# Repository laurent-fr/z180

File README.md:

# Micro Z180 homebrew computer

*This is my attempt to create a 80's style computer based on the Zilog Z180 CPU.*

The goal is to build from scratch a complete computer, with  keyboard, video display, and mass storage. The software will be Microsoft BASIC and CP/M. Think of it as a crossover between an Amstrad CPC and an IBM PC 5150 !

The computer is designed around STEBUS, which is an old but well designed 8-bits industry-standard bus (https://en.wikipedia.org/wiki/STEbus). 

For now there are 5 cards :

 * PSU : the power supply, which takes 12v as input and generates +5v and -12v 
 * BUS : the STEBUS base board, with 5 slots and active termination
 * CPU : The main CPU board, with 2 RS-232 connectors
 * VDU : Video display unit, VGA text-only 80x25 with 16 colors, and 8 fonts selectable via jumpers on the board
 * MIO : Multi I/O, including PS/2 keyboard, Real time clock, Sound , Compact flash and Parallel port
 
 There are 3 main folders in this reposirory :
 
 * enclosure : all the files needed to build the case, which is laser-cut 3mm transparent acrylic (all parts are smaller than 200x300 mm), with a 3D printed part to mechanicaly guide the boards.
 * hardware : the description of all boards (very incomplete for now !)
 * software : Tests, BIOS, BASIC, and CP/M (coming soon !)
 
 ## Licenses
 
All the software is GPL v2, and all the hardware is CC-BY-NC-SA
 
 ## Status of the computer
 
 **This is a work-in-progress !**
 
 For now the computer is running BASIC with the PS/2 keyboard and integrated video display. There are still some rough edges but we are almost here.
 
 Some files are not yet on the repository because the computer was designed with paper and pencil !

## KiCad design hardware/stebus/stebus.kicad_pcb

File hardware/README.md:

# Hardware

## Software needed

A few softwares are needed for reading/using the files in this folder :

* Kicad for reading the schematics and board layouts  https://kicad-pcb.org/ 
* Quartus 2 web edition for programming the Altera CPLDs https://fpgasoftware.intel.com/13.1/?edition=web
* WinCUPL for programming the GAL of the VDU board https://www.microchip.com/design-centers/fpgas-and-plds/splds-cplds/pld-design-resources

Optional :

* LTSPice, if you want to look at the few simulation files https://www.analog.com/en/design-center/design-tools-and-calculators/ltspice-simulator.html

## Hardware needed for running the computer

* An EPROM programmer. I use a Minipro TL866.
* A JTAG programmer for the CPLDs. I use the super cheap USB Blaster.

## Hardware for debugging the computer

It is not strictly needed to build the computer from the blueprints, but if something goes wrong the following could help :

* An EPROM simulator. The fastest way to test a new firmware ! Mine is a MemSIM2 from http://www.momik.pl/ and it works very well.
* A logic analyzer. Pick your favourite. Mine is a DSLogic.
* A good old oscilloscope is useful, too !

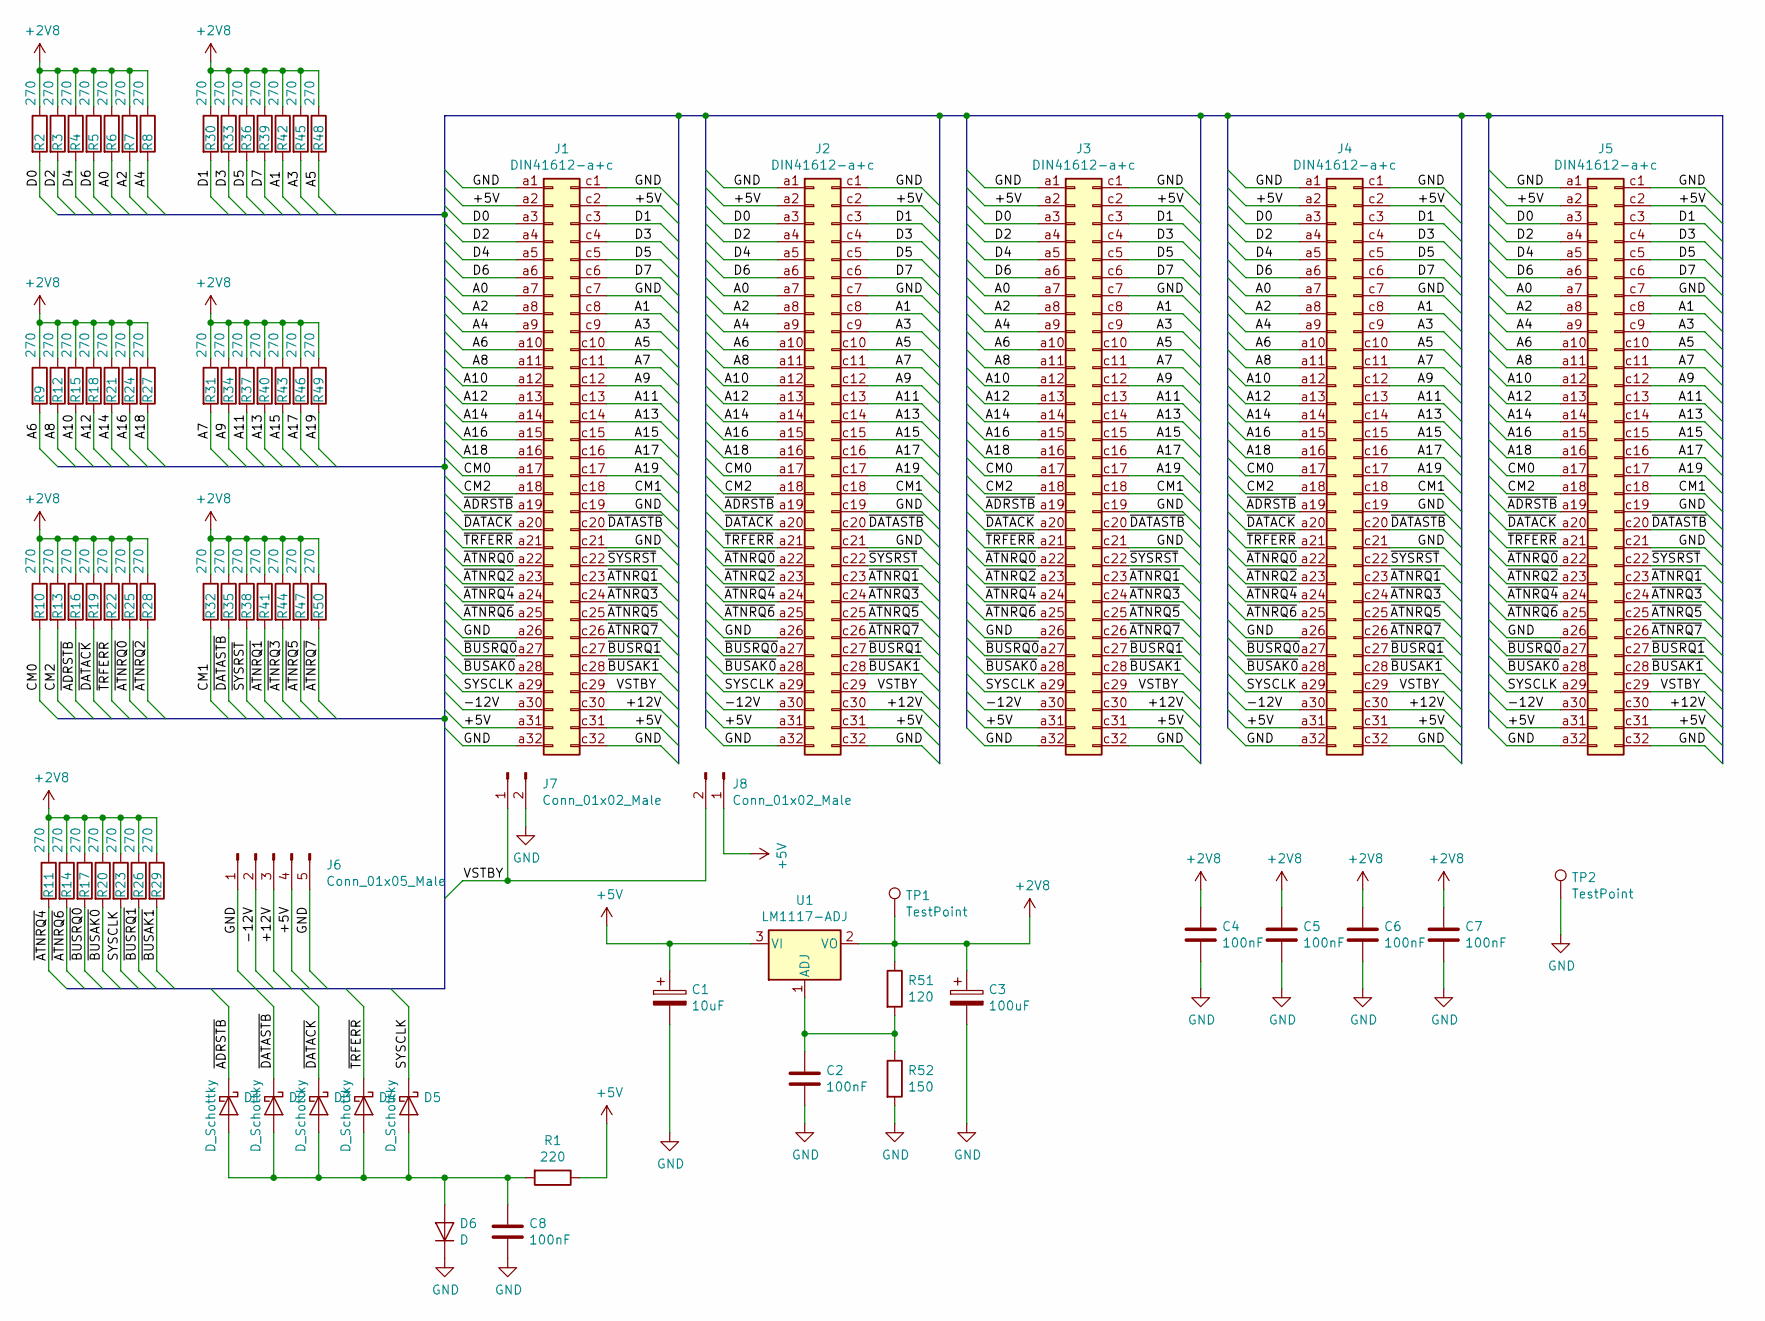
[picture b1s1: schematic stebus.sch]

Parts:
C1: 10uF; C_1210_HandSoldering
C2, C4, C5, C6, C7, C8: 100nF; C_1206_HandSoldering
C3: 100uF; C_1812_HandSoldering
D1, D2, D3, D4, D5: D_Schottky; D_SMA
D6: D; D_MiniMELF_Handsoldering
J1, J2, J3, J4, J5: DIN41612-a+c; Socket_DIN41612-CaseC1-AC-Female-64Pin-2rows
J6: Conn_01x05_Male; Molex_MiniFit-JR-5556-10A_1x05x4.20mm_Straight
J7: Conn_01x02_Male; Molex_KK-6410-02_02x2.54mm_Straight
J8: Conn_01x02_Male; Pin_Header_Straight_1x02_Pitch2.54mm
R1: 220; R_1206_HandSoldering
R2, R3, R4, R5, R6, R7, R8, R9, R10, R11, R12, R13, R14, R15, R16, R17, R18, R19, R20, R21, R22, R23, R24, R25, R26, R27, R28, R29, R30, R31, R32, R33, R34, R35, R36, R37, R38, R39, R40, R41, R42, R43, R44, R45, R46, R47, R48, R49, R50: 270; R_1206_HandSoldering
R51: 120; C_1206_HandSoldering
R52: 150; C_1206_HandSoldering
TP1, TP2: TestPoint; Pin_Header_Straight_1x01_Pitch2.54mm
U1: LM1117-ADJ; SOT-223-3_TabPin2

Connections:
+2V8: C3.1, C4.1, C5.1, C6.1, C7.1, R2.1, R3.1, R4.1, R5.1, R6.1, R7.1, R8.1, R9.1, R10.1, R11.1, R12.1, R13.1, R14.1, R15.1, R16.1, R17.1, R18.1, R19.1, R20.1, R21.1, R22.1, R23.1, R24.1, R25.1, R26.1, R27.1, R28.1, R29.1, R30.1, R31.1, R32.1, R33.1, R34.1, R35.1, R36.1, R37.1, R38.1, R39.1, R40.1, R41.1, R42.1, R43.1, R44.1, R45.1, R46.1, R47.1, R48.1, R49.1, R50.1, R51.1, TP1.1, U1.2 (VO)
+5V: C1.1, J1.a2, J1.a31, J1.c2, J1.c31, J2.a2, J2.a31, J2.c2, J2.c31, J3.a2, J3.a31, J3.c2, J3.c31, J4.a2, J4.a31, J4.c2, J4.c31, J5.a2, J5.a31, J5.c2, J5.c31, J6.4, J8.1, R1.1, U1.3 (VI)
/+12V: J1.c30, J2.c30, J3.c30, J4.c30, J5.c30, J6.3
/-12V: J1.a30, J2.a30, J3.a30, J4.a30, J5.a30, J6.2
/A0: J1.a7, J2.a7, J3.a7, J4.a7, J5.a7, R6.2
/A1: J1.c8, J2.c8, J3.c8, J4.c8, J5.c8, R42.2
/A2: J1.a8, J2.a8, J3.a8, J4.a8, J5.a8, R7.2
/A3: J1.c9, J2.c9, J3.c9, J4.c9, J5.c9, R45.2
/A4: J1.a9, J2.a9, J3.a9, J4.a9, J5.a9, R8.2
/A5: J1.c10, J2.c10, J3.c10, J4.c10, J5.c10, R48.2
/A6: J1.a10, J2.a10, J3.a10, J4.a10, J5.a10, R9.2
/A7: J1.c11, J2.c11, J3.c11, J4.c11, J5.c11, R31.2
/A8: J1.a11, J2.a11, J3.a11, J4.a11, J5.a11, R12.2
/A9: J1.c12, J2.c12, J3.c12, J4.c12, J5.c12, R34.2
/A10: J1.a12, J2.a12, J3.a12, J4.a12, J5.a12, R15.2
/A11: J1.c13, J2.c13, J3.c13, J4.c13, J5.c13, R37.2
/A12: J1.a13, J2.a13, J3.a13, J4.a13, J5.a13, R18.2
/A13: J1.c14, J2.c14, J3.c14, J4.c14, J5.c14, R40.2
/A14: J1.a14, J2.a14, J3.a14, J4.a14, J5.a14, R21.2
/A15: J1.c15, J2.c15, J3.c15, J4.c15, J5.c15, R43.2
/A16: J1.a15, J2.a15, J3.a15, J4.a15, J5.a15, R24.2
/A17: J1.c16, J2.c16, J3.c16, J4.c16, J5.c16, R46.2
/A18: J1.a16, J2.a16, J3.a16, J4.a16, J5.a16, R27.2
/A19: J1.c17, J2.c17, J3.c17, J4.c17, J5.c17, R49.2
/CM0: J1.a17, J2.a17, J3.a17, J4.a17, J5.a17, R10.2
/CM1: J1.c18, J2.c18, J3.c18, J4.c18, J5.c18, R32.2
/CM2: J1.a18, J2.a18, J3.a18, J4.a18, J5.a18, R13.2
/D0: J1.a3, J2.a3, J3.a3, J4.a3, J5.a3, R2.2
/D1: J1.c3, J2.c3, J3.c3, J4.c3, J5.c3, R30.2
/D2: J1.a4, J2.a4, J3.a4, J4.a4, J5.a4, R3.2
/D3: J1.c4, J2.c4, J3.c4, J4.c4, J5.c4, R33.2
/D4: J1.a5, J2.a5, J3.a5, J4.a5, J5.a5, R4.2
/D5: J1.c5, J2.c5, J3.c5, J4.c5, J5.c5, R36.2
/D6: J1.a6, J2.a6, J3.a6, J4.a6, J5.a6, R5.2
/D7: J1.c6, J2.c6, J3.c6, J4.c6, J5.c6, R39.2
/SYSCLK: D5.1 (K), J1.a29, J2.a29, J3.a29, J4.a29, J5.a29, R23.2
/VSTBY: J1.c29, J2.c29, J3.c29, J4.c29, J5.c29, J7.1, J8.2
/~: J1.a25, J2.a25, J3.a25, J4.a25, J5.a25, R14.2
/~ADRSTB~: D1.1 (K), J1.a19, J2.a19, J3.a19, J4.a19, J5.a19, R16.2
/~ATNRQ0~: J1.a22, J2.a22, J3.a22, J4.a22, J5.a22, R25.2
/~ATNRQ1~: J1.c23, J2.c23, J3.c23, J4.c23, J5.c23, R41.2
/~ATNRQ2~: J1.a23, J2.a23, J3.a23, J4.a23, J5.a23, R28.2
/~ATNRQ3~: J1.c24, J2.c24, J3.c24, J4.c24, J5.c24, R44.2
/~ATNRQ4~: J1.a24, J2.a24, J3.a24, J4.a24, J5.a24, R11.2
/~ATNRQ5~: J1.c25, J2.c25, J3.c25, J4.c25, J5.c25, R47.2
/~ATNRQ7~: J1.c26, J2.c26, J3.c26, J4.c26, J5.c26, R50.2
/~BUSAK0~: J1.a28, J2.a28, J3.a28, J4.a28, J5.a28, R20.2
/~BUSAK1~: J1.c28, J2.c28, J3.c28, J4.c28, J5.c28, R29.2
/~BUSRQ0~: J1.a27, J2.a27, J3.a27, J4.a27, J5.a27, R17.2
/~BUSRQ1~: J1.c27, J2.c27, J3.c27, J4.c27, J5.c27, R26.2
/~DATACK~: D3.1 (K), J1.a20, J2.a20, J3.a20, J4.a20, J5.a20, R19.2
/~DATASTB~: D2.1 (K), J1.c20, J2.c20, J3.c20, J4.c20, J5.c20, R35.2
/~SYSRST~: J1.c22, J2.c22, J3.c22, J4.c22, J5.c22, R38.2
/~TRFERR~: D4.1 (K), J1.a21, J2.a21, J3.a21, J4.a21, J5.a21, R22.2
GND: C1.2, C2.2, C3.2, C4.2, C5.2, C6.2, C7.2, C8.2, D6.1 (K), J1.a1, J1.a26, J1.a32, J1.c1, J1.c7, J1.c19, J1.c21, J1.c32, J2.a1, J2.a26, J2.a32, J2.c1, J2.c7, J2.c19, J2.c21, J2.c32, J3.a1, J3.a26, J3.a32, J3.c1, J3.c7, J3.c19, J3.c21, J3.c32, J4.a1, J4.a26, J4.a32, J4.c1, J4.c7, J4.c19, J4.c21, J4.c32, J5.a1, J5.a26, J5.a32, J5.c1, J5.c7, J5.c19, J5.c21, J5.c32, J6.1, J6.5, J7.2, R52.2, TP2.1
unnamed: C2.1, R51.2, R52.1, U1.1 (ADJ)
unnamed: C8.1, D1.2 (A), D2.2 (A), D3.2 (A), D4.2 (A), D5.2 (A), D6.2 (A), R1.2

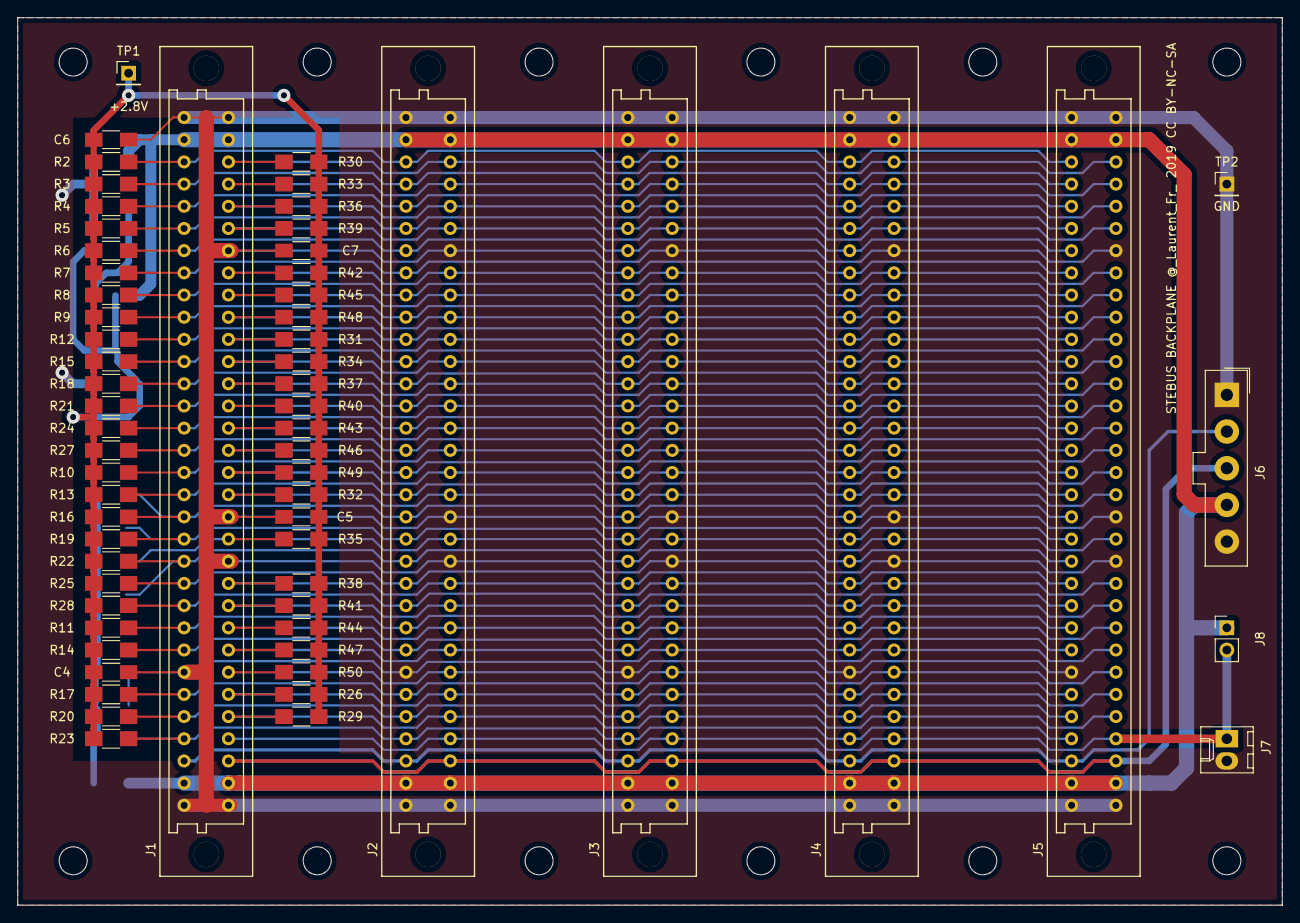
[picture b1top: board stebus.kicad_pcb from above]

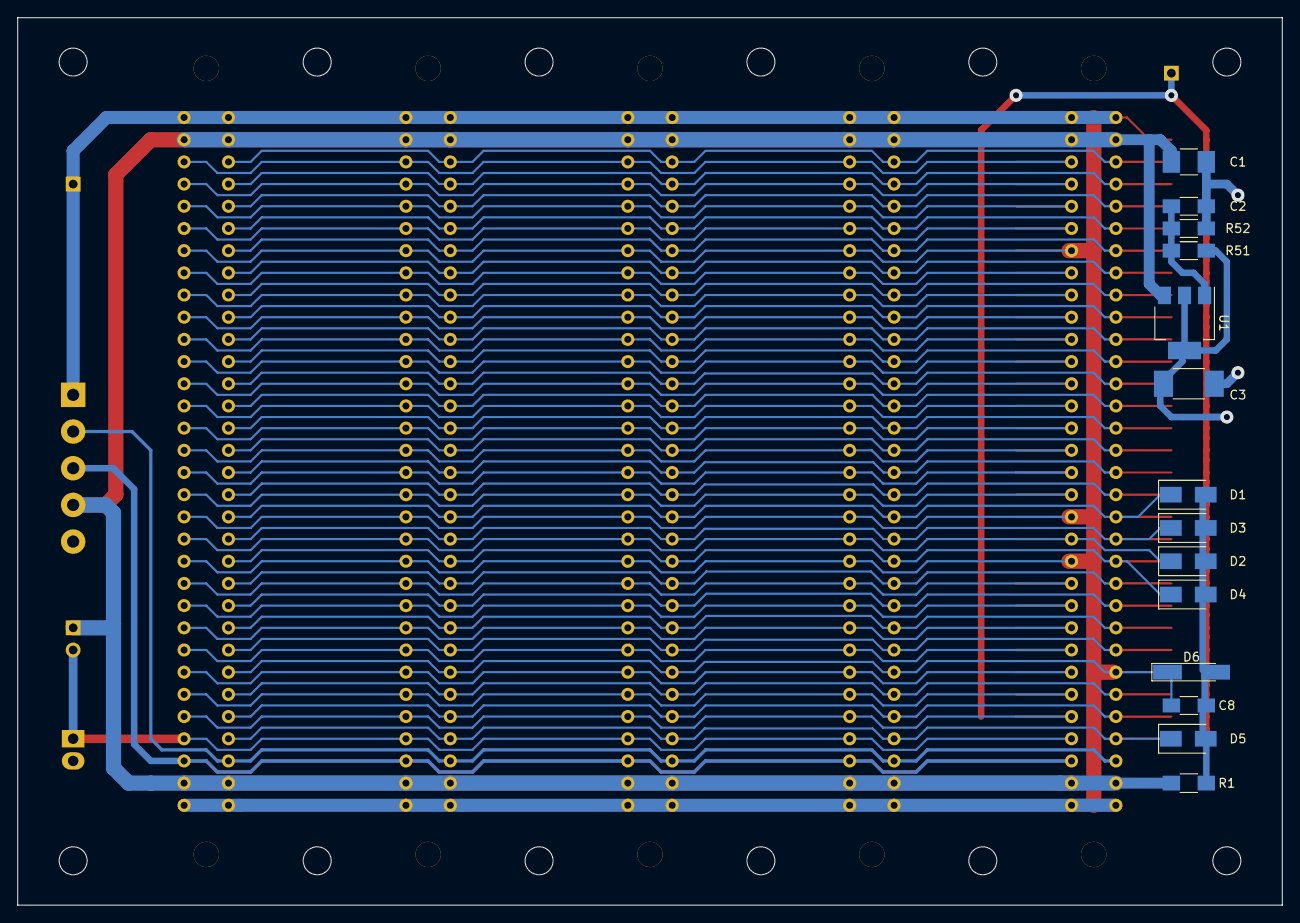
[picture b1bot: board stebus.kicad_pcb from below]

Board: 2 copper layers, 144.8 x 101.6 mm, 77 parts (14 on the bottom side), 57 nets.

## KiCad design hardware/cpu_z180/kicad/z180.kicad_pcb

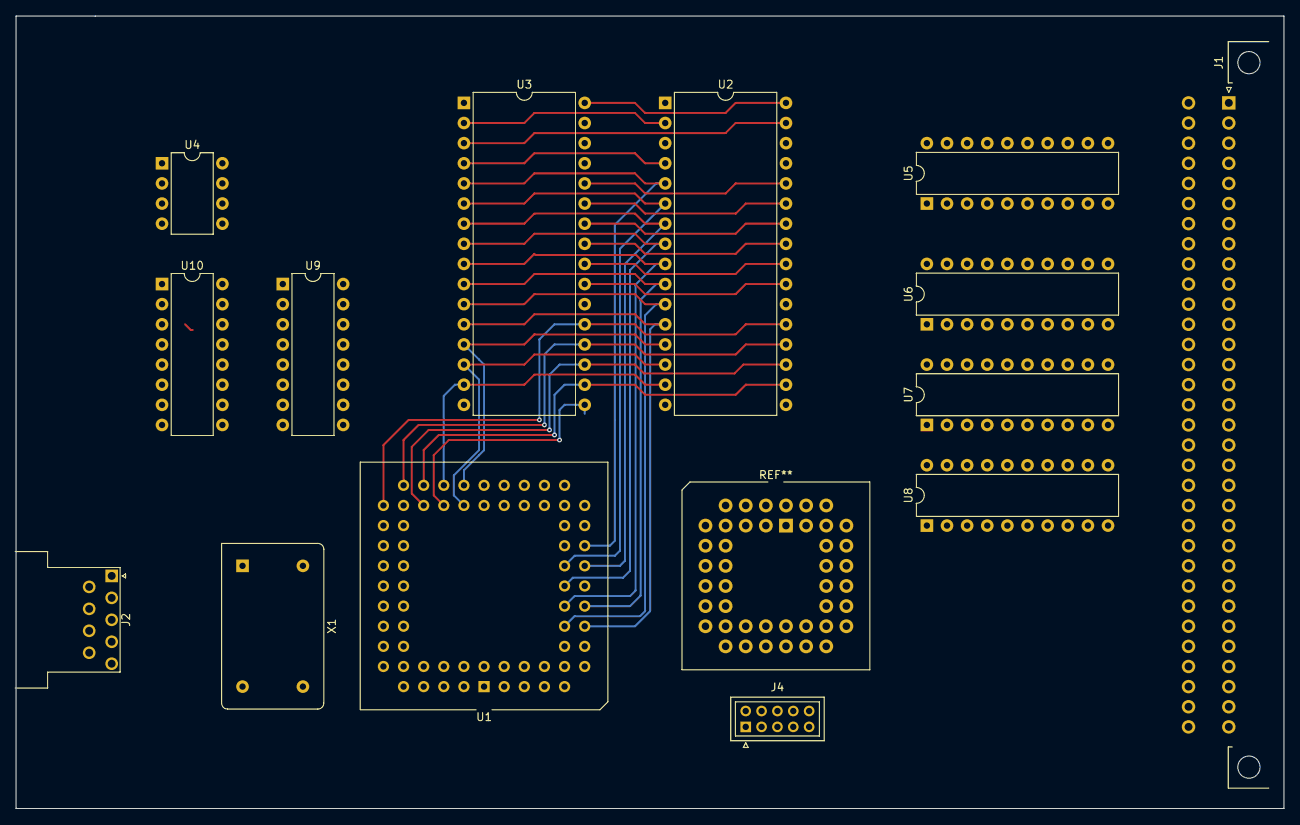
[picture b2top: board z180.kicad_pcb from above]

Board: 2 copper layers, 160.0 x 100.0 mm, 14 parts (0 on the bottom side), 61 nets.

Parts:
J1: DIN41612-a+c; DIN41612_A+C_2x32_Horizontal
J2: DB9_Male_MountingHoles; DSUB-9_Male_Horizontal_P2.77x2.84mm_EdgePinOffset9.40mm
J4: Conn_02x05_Counter_Clockwise; JAE_LY20-10P-2T_2x05x2.00mm_Straight
U1: Z8S180CPU; PLCC-68_THT-Socket
U2: AS6C4008-55PCN; DIP-32_W15.24mm
U3: 27C010; DIP-32_W15.24mm
U4: TL7705B; DIP-8_W7.62mm
U5, U6, U7, U8: 74HC245; DIP-20_W7.62mm
U9, U10: MAX232; DIP-16_W7.62mm
X1: ACO-xxxMHz; Oscillator_DIP-14

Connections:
+5V: J1.a2, J1.a31, J1.c2, J1.c31, U1.34, U2.32, U3.31, U3.32, U5.20, X1.14
/bus-z180/BUS_A0: J1.a7, U6.18
/bus-z180/BUS_A1: J1.c8, U6.17
/bus-z180/BUS_A2: J1.a8, U6.16
/bus-z180/BUS_A3: J1.c9, U6.15
/bus-z180/BUS_A4: J1.a9, U6.14
/bus-z180/BUS_A5: J1.c10, U6.13
/bus-z180/BUS_A6: J1.a10, U6.12
/bus-z180/BUS_A7: J1.c11, U6.11
/bus-z180/BUS_A8: J1.a11, U7.18
/bus-z180/BUS_A9: J1.c12, U7.17
/bus-z180/BUS_A10: J1.a12, U7.16
/bus-z180/BUS_A11: J1.c13, U7.15
/bus-z180/BUS_A12: J1.a13, U7.14
/bus-z180/BUS_A13: J1.c14, U7.13
/bus-z180/BUS_A14: J1.a14, U7.12
/bus-z180/BUS_A15: J1.c15, U7.11
/bus-z180/BUS_A16: J1.a15, U8.18
/bus-z180/BUS_A17: J1.c16, U8.17
/bus-z180/BUS_A18: J1.a16, U8.16
/bus-z180/BUS_A19: J1.c17, U8.15
/bus-z180/BUS_D0: J1.a3, U5.18
/bus-z180/BUS_D1: J1.c3, U5.17
/bus-z180/BUS_D2: J1.a4, U5.16
/bus-z180/BUS_D3: J1.c4, U5.15
/bus-z180/BUS_D4: J1.a5, U5.14
/bus-z180/BUS_D5: J1.c5, U5.13
/bus-z180/BUS_D6: J1.a6, U5.12
/bus-z180/BUS_D7: J1.c6, U5.11
/~RD~: U1.67, U2.24, U3.24
/~WR~: U1.66, U2.29
A0: U1.14, U2.12, U3.12, U6.2
A1: U1.15, U2.11, U3.11, U6.3
A2: U1.16, U2.10, U3.10, U6.4
A3: U1.17, U2.9, U3.9, U6.5
A4: U1.19, U2.8, U3.8, U6.6
A5: U1.20, U2.7, U3.7, U6.7
A6: U1.21, U2.6, U3.6, U6.8
A7: U1.22, U2.5, U3.5, U6.9
A8: U1.23, U2.27, U3.27, U7.2
A9: U1.24, U2.26, U3.26, U7.3
A10: U1.25, U2.23, U3.23, U7.4
A11: U1.26, U2.25, U3.25, U7.5
A12: U1.27, U2.4, U3.4, U7.6
A13: U1.28, U2.28, U3.28, U7.7
A14: U1.29, U2.3, U3.29, U7.8
A15: U1.30, U2.31, U3.3, U7.9
A16: U1.31, U2.2, U3.2, U8.2
A17: U1.32, U2.30, U8.3
A18: U1.33, U2.1, U8.4
A19: U1.35, U8.5
D0: U1.37, U2.13, U3.13, U5.2
D1: U1.38, U2.14, U3.14, U5.3
D2: U1.39, U2.15, U3.15, U5.4
D3: U1.40, U2.17, U3.17, U5.5
D4: U1.41, U2.18, U3.18, U5.6
D5: U1.42, U2.19, U3.19, U5.7
D6: U1.43, U2.20, U3.20, U5.8
D7: U1.44, U2.21, U3.21, U5.9
GND: J1.a1, J1.a26, J1.a32, J1.c1, J1.c7, J1.c19, J1.c21, J1.c32, U1.1, U1.2, U1.18, U1.36, U2.16, U3.1, U3.16, U5.10, X1.7
unnamed: U1.4, X1.8

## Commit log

2019-12-03 Hello World / SDCC
2019-12-04 Nascom BASIC
2019-12-04 basic patch
2019-12-05 BASIC matches original
2019-12-05 adding NASCOM BASIC patched by Grant Searle from archive.org
2019-12-06 Basic / SBASM
2019-12-07 kicad - stebus
2019-12-07 monitor - rx routine
2020-01-06 vdu files
2020-01-07 fonts
2020-01-08 font file
2020-01-12 vdu update
2020-04-18 'keyboard'
2020-04-19 keyboard decoder
2020-04-19 clavier
2020-04-25 'eprom.hex'
2020-04-26 'bios'
2020-04-29 'basic'
2020-05-01 3d files
2020-05-01 back corner
2020-05-02 corner
2020-05-02 'dxf'
2020-05-02 bottom
2020-05-02 front in
2020-05-03 'enclosure'
2020-05-03 case
2020-05-08 keyboard debug
2020-05-09 top psu
2020-05-09 dxf bugfix
2020-05-10 cursor bugfix + top right vdu bugfix
2020-05-10 color in BASIC
2020-05-11 bugfix
2020-05-17 repo cleanup
2020-05-17 Test software README
2020-05-17 Software README
2020-05-17 picture of the computer
2020-05-17 photo
2020-05-17 fixing typos
2020-05-17 link to SBASM
2020-05-17 Hardware README
2020-05-17 typo
2020-05-17 fix include path
2020-05-17 testing test_mio_cf

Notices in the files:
hardware/stebus/stebus.kicad_pcb:
STEBUS BACKPLANE @_Laurent_Fr_ 2019 CC BY-NC-SA
